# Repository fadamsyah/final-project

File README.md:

# final-project
Control of Autonomous Golf Cart. This repository includes low-level controller and high-level controller.

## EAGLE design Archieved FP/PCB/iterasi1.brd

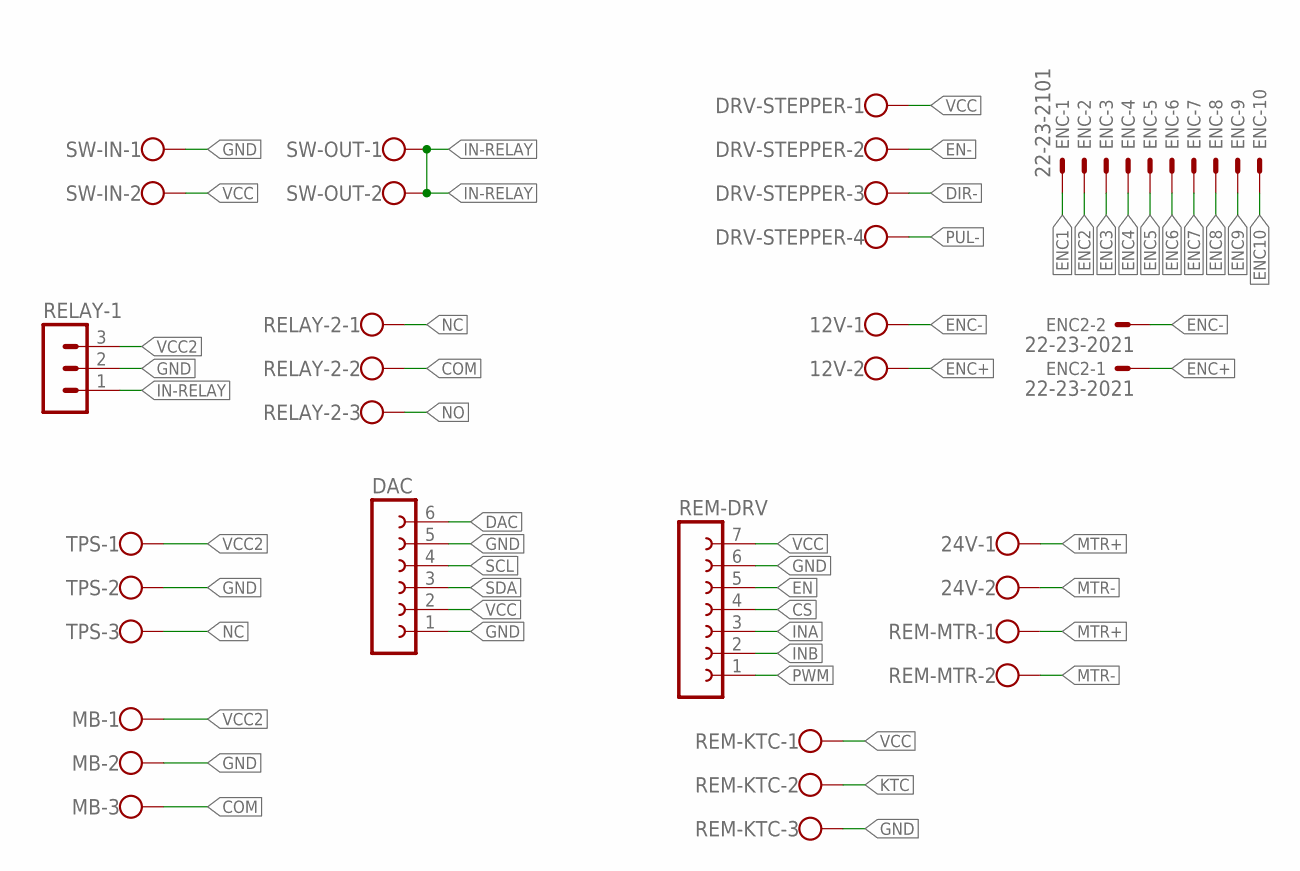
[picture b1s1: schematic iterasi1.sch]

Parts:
12V, 24V: W237-102
DAC: FE06-1; FE06
DRV-STEPPER: W237-4
ENC: 22-23-2101
ENC2: 22-23-2021
MB: W237-103
RELAY-1: MA03-1
RELAY-2: W237-103
REM-DRV: FE07-1; FE07
REM-KTC: W237-103
REM-MTR: W237-102
SW-IN: W237-102
SW-OUT: W237-102
TPS: W237-103

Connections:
COM: MB.3, RELAY-2.2
CS: REM-DRV.4
DAC: DAC.6
DIR-: DRV-STEPPER.3
EN: REM-DRV.5
EN-: DRV-STEPPER.2
ENC1: ENC.1
ENC2: ENC.2
ENC3: ENC.3
ENC4: ENC.4
ENC5: ENC.5
ENC6: ENC.6
ENC7: ENC.7
ENC8: ENC.8
ENC9: ENC.9
ENC10: ENC.10
ENC+: 12V.2, ENC2.1
ENC-: 12V.1, ENC2.2
GND: DAC.1, DAC.5, MB.2, RELAY-1.2, REM-DRV.6, REM-KTC.3, SW-IN.1, TPS.2
IN-RELAY: RELAY-1.1, SW-OUT.1, SW-OUT.2
INA: REM-DRV.3
INB: REM-DRV.2
KTC: REM-KTC.2
MTR+: 24V.1, REM-MTR.1
MTR-: 24V.2, REM-MTR.2
NC: RELAY-2.1, TPS.3
NO: RELAY-2.3
PUL-: DRV-STEPPER.4
PWM: REM-DRV.1
SCL: DAC.4
SDA: DAC.3
VCC: DAC.2, DRV-STEPPER.1, REM-DRV.7, REM-KTC.1, SW-IN.2
VCC2: MB.1, RELAY-1.3, TPS.1

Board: 2 copper layers, 15 parts (0 on the bottom side), 10 nets, no tracks yet.

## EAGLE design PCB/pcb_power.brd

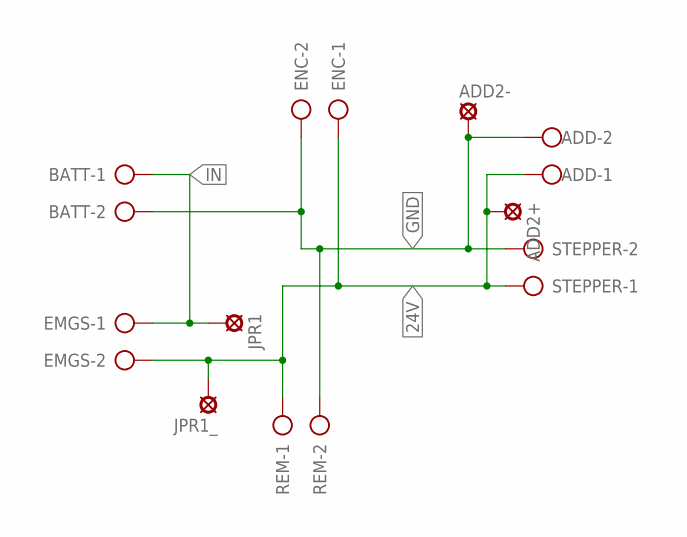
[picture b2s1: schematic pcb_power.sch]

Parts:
ADD: W237-102
ADD2+, ADD2-: SE14
BATT: W237-102
EMGS: W237-102
ENC: W237-102
JPR1, JPR1_: SE14
REM: W237-102
STEPPER: W237-102

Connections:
24V: ADD.1, ADD2+.MP, EMGS.2, ENC.1, JPR1_.MP, REM.1, STEPPER.1
GND: ADD.2, ADD2-.MP, BATT.2, ENC.2, REM.2, STEPPER.2
IN: BATT.1, EMGS.1, JPR1.MP

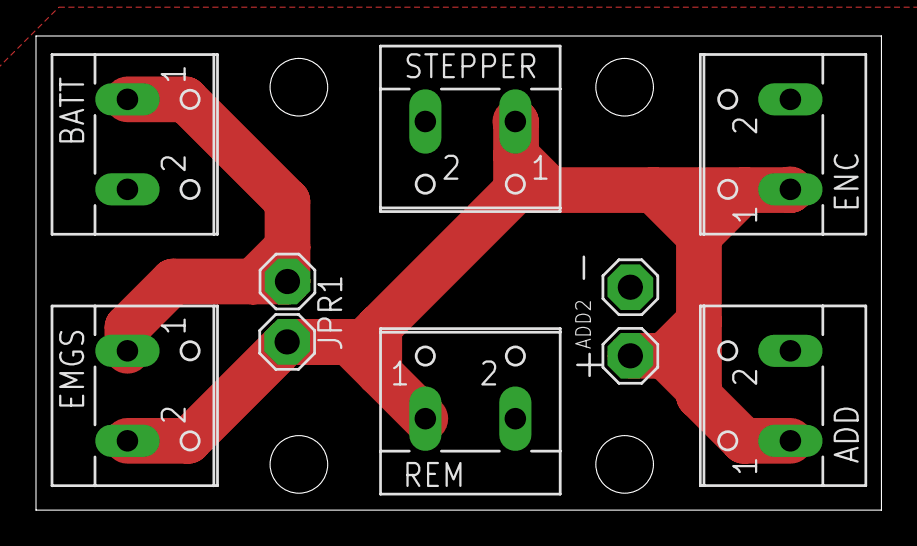
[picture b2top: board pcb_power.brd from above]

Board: 2 copper layers, 47.0 x 26.3 mm, 10 parts (0 on the bottom side), 3 nets.

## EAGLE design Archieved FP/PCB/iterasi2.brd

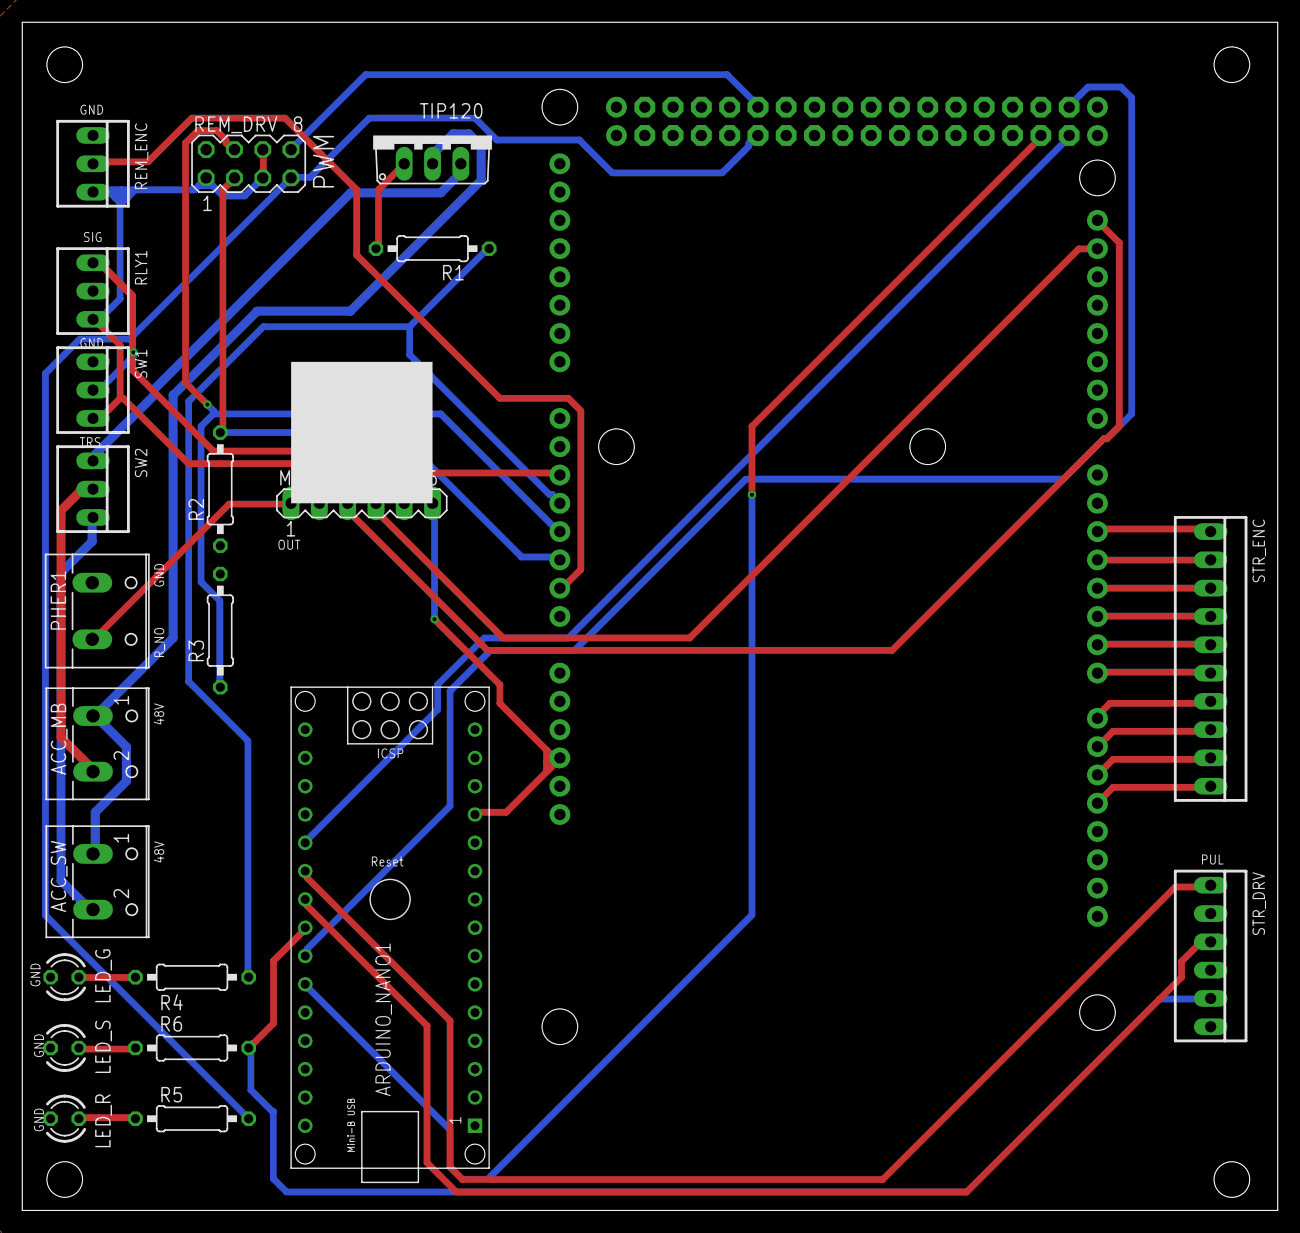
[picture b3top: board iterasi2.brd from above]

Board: 2 copper layers, 112.7 x 106.7 mm, 23 parts (1 on the bottom side), 36 nets.

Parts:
ACC_MB: W237-102
ACC_SW: W237-102
ARDUINO_NANO1: ARDUINO_NANO
B1: ARDUINO_MEGA_R3FULL; ARDUINO_MEGA
LED_G: TLLY4400; LED3MM
LED_R: TLLY4400; LED3MM
LED_S: TLLY4400; LED3MM
MCP4725: MA06-1
PHER1: GND_TPS/RELAY_NO; W237-132
R1: 5k1; 0207/10
R2, R3: 680; 0207/10
R4, R5, R6: 220; 0207/10
REM_DRV: MA04-2
REM_ENC: 22-23-2031
RLY1: 22-23-2031
STR_DRV: 22-23-2061
STR_ENC: 22-23-2101
SW1, SW2: 22-23-2031
TIP120: TIP41C; TO220AV

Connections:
5V: ARDUINO_NANO1.12, B1.5V@0, MCP4725.6, REM_DRV.1, REM_DRV.5, REM_DRV.6, REM_ENC.3, RLY1.3, SW1.3
48V: ACC_MB.1, ACC_SW.1, TIP120.C
F_MODE: B1.A5, RLY1.1, SW1.2
GAS_EN: B1.A4, R1.1, R4.2
GAS_SIG: MCP4725.1, PHER1.2
GND: ARDUINO_NANO1.14, ARDUINO_NANO1.19, B1.GND@0, B1.GND@1, B1.GND@2, B1.GND@3, B1.GND@4, LED_G.K, LED_R.K, LED_S.K, MCP4725.2, MCP4725.5, PHER1.1, R2.1, R3.2, REM_DRV.2, REM_ENC.1, RLY1.2, STR_DRV.2, STR_DRV.4, STR_DRV.6, SW1.1
L_IS: B1.A3, R3.1, REM_DRV.4
L_PWM: B1.45, REM_DRV.8
unnamed: R1.2, TIP120.B
unnamed: SW2.1, TIP120.E
unnamed: ACC_MB.2, SW2.2
unnamed: ACC_SW.2, SW2.3
unnamed: LED_G.A, R4.1
unnamed: LED_R.A, R5.1
unnamed: LED_S.A, R6.1
unnamed: ARDUINO_NANO1.20, B1.22
unnamed: ARDUINO_NANO1.24, B1.23
unnamed: ARDUINO_NANO1.25, B1.24
REM_ENC: B1.A1, REM_ENC.2
R_IS: B1.A2, R2.2, REM_DRV.3
R_PWM: B1.44, R5.2, REM_DRV.7
SCL: B1.21, MCP4725.3
SDA: B1.20, MCP4725.4
SEN1: B1.2, STR_ENC.1
SEN2: B1.3, STR_ENC.2
SEN3: B1.4, STR_ENC.3
SEN4: B1.5, STR_ENC.4
SEN5: B1.6, STR_ENC.5
SEN6: B1.7, STR_ENC.6
SEN7: B1.8, STR_ENC.7
SEN8: B1.9, STR_ENC.8
SEN9: B1.10, STR_ENC.9
SEN10: B1.11, STR_ENC.10
STR_DIR: ARDUINO_NANO1.22, STR_DRV.3
STR_ENA: ARDUINO_NANO1.23, R6.2, STR_DRV.5
STR_PUL: ARDUINO_NANO1.21, STR_DRV.1

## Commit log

2020-07-24 - Make the low-level-controller - Add the brake_log_mega using BTS 7960 driver
2020-07-24 Add a ROS package named 'pkg_ta'
2020-07-24 Add two additional informations to the message: 1) string brake_state 2) string steering_state
    Change some data type of the informations of brake:
    1) brake_linear_encoder ~ int32 --> float32
    2) signal from current sensor ~ int32 --> float32
    Add right and left current sensor:
    1) float32 brake_R_IS
    2) float32 brake_L_IS
2020-07-24 Update the brake_log_mega_bts7960 including: 1) Add some additional informations to the Brake message 2) Divide the sensing_braking into sensing_braking_position & sensing_braking_current
2020-07-24 Add mega_implementation.ino
2020-07-24 Add the mega_implementation.ino
2020-07-25 Add the stepper_nano.ino file
2020-07-25 Optimize the stepper_nano file and fix a prospective bug 1) Delete all of the unnecessary line, e.g. Serial.begin and Serial.println 2) Change a variable name, i.e. now --> dt 3) Fix a prospective bu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
2020-07-29 Add the ROX.txt file and update the mega_implementation: 1) Add the throttle code in mega_implementation 2) Comment the state message in Arduino because of error. The string message should be sent co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
2020-08-02 Add the pre-made drawio file describing the diagram block
2020-08-03 Initialize the data branch
2020-08-03 Add some files: 1. .gitignore files ignoring .ipynb_checkpoints 2. Add the absolute encoder calibration data and notebook 3. Add the linear transduser calibration data 4. Add the rosbag data
2020-08-03 Make some linear regression models for absolute encoder and linear transduser sensor
2020-08-05 Add the absolute encoder calibration
2020-08-05 Add a .ipynb estimating how long the Arduino takes to accelerate the stepper motor and optimize the stepper motor code.
2020-08-06 Edit the calibration plot
2020-08-06 Convert the steering angle from radian to degree
2020-08-07 Change the maximum and minimum value command from a joystitck
2020-08-07 Add the .gitignore file ignoring .ipynb_checkpoints/ and __pycache__/
2020-08-07 Add the controller_2D.py file as the high level controller
2020-08-07 Add the UNCOMPLETE control.py file
2020-08-09 Add the waypoints
2020-08-09 Use the exponential moving average algorithm to make the joystick signal smoother.
2020-08-09 Edit the .gitignore file
2020-08-10 Test the joystick.py, fix some bugs in that file, and add the steer, throttle, and brake threshold.
2020-08-10 Add some additional variables into Control.msg and edit the joystick.py
2020-08-10 Change the sub_msg.<var> to sub_msg.action_<var> in Arduino to match the newest Control.msg
2020-08-11 Fix some bugs, i.e.: 1) Change the DIR dan PUL pin 2) Change the stepper acceleration 3) Make the Arduino Mega sends the interrupt signal to the Arduino Mega every update_steering_period
2020-08-11 Make two different coefficients to calculate the longitudinal dan lateral control signal using exponential moving average (EMA)
2020-08-11 Add the control deadband to control the steering angle
2020-08-11 Laporan TA @11 August 2020
2020-08-12 Evaluation @ 12 August 2020: 1. Change steering_delta_min_move to 0.3 degree 2. Change the acceleration of the stepper motor 3. Change the max_throttle to 0.5 in joystick.py file 4. Add the log_steer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
2020-08-12 Analyze and visualize the movement of steering angle.
2020-08-13 Add some additional lines to the UNOMPLETED control.py file
2020-08-13 Edit the PWM setting in the log_brake.ino file
2020-08-13 Add the UNCOMPLETE brake calibration
2020-08-13 Evaluation @13 August 2020: 1) Add the LogBrakeCommand.msg 2) Edit the CMakeLists.txt to include LogBrakeCommand.msg 3) Edit the maximum throttle value in joystick.py 4) Add the log_brake.py and the 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
2020-08-13 Compare the Quaternion --> RPY Conversion from tf and Coursera
2020-08-13 Add the interpolated waypoints
2020-08-13 Complete the control.py file, add the waypoints, and move the log python file to the /log_low_level/ folder
2020-08-14 Limit the change of the throttle voltage
2020-08-14 Change the maximum value of the throttle output
2020-08-14 Plot the brake data
2020-08-14 Add the pwm sign to brake_pwm so that we know whether the motor is PULLING or RELEASING
2020-08-14 Edit the architecture of steering control
2020-08-15 Add some additional information regarding the steering and brake performance
2020-08-17 Add the kalman filter for estimate the state from GPS data only
2020-08-17 Add the kf_gps class optimized using Numba
2020-08-17 ROS Error. Save file dulu
2020-08-17 Add the ROS gps state estimation program
2020-08-17 Add the angular rate correction
2020-08-17 Add the waypoints' bag
2020-08-17 Add the kf_gps test
2020-08-18 Generate some new waypoints
2020-08-18 Add the new lab waypoints
2020-08-18 pkg_ta MAJOR CHANGE: 1) Move the controller_2D.py and kf_gps.py (containing some classes) to lib_ta_py/ 2) Solve a bug regarding the lateral saturation value in controller_2D.py 3) Make the bag/ fold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
2020-08-19 MAJOR UPDATE: 1) Add new generate_waypoints_CEPAT folder 2) Log step response 3) Tune the stanley controller in control_with_gps.py 4) Ada data yang berhasil diambil (lateral control)
2020-08-19 Add step response data & 2 percobaan yang berhasil (lateral control)
2020-08-19 Plot beberapa informasi menarik
2020-08-19 Cek data longitudinal yang dikirim Atwin
2020-08-20 Add some plots regarding the result of 'data_yang_berhasil'
2020-08-22 Add some plot to log_longitudinal/dari_atwin/cek_data.ipynb
2020-08-22 Add a CARLA simulation folder
2020-08-22 Add the simulation plot and result
2020-08-22 Fix some bugs
2020-08-22 Organize some files and add the longitudinal data
2020-08-23 Get longitudinal data for simulation
2020-08-24 Add some new log steering data
2020-08-24 Edit the stepper timing and add some code to overcome the stepper stalling phenomena
2020-08-24 pkg_TA @24 August 2020
2020-08-25 Progress @25 August 2020
2020-08-25 PROGRESS @25 Agustus 2020
2020-08-25 Add some additional analysis
2020-08-26 PROGRESS @26 Agustus 2020
2020-08-26 Add some additional experiment data (26 Agustus 2020)
2020-08-26 Lateral Control with error lateral only: Proportional-Derivative
2020-08-26 Add additional data and code to generate waypoints
2020-08-26 New ROS-control file for final project
2020-08-26 Add a .ipynb that generate a new set of waypoints from the 26_agus_wp by shifting the initial position
2020-08-26 Fix a bug. The x and y shift must be calculated at a specific point for every set of waypoints
2020-08-27 Progress 27 Agustus 2020 (PAGI)
2020-08-27 Plot some experiment results
2020-08-27 PROGRESS @ 27 Agustus 2020
2020-08-28 Make the EDIT_WAYPOINTS notebook to automatically update all of the set of waypoints. Add some new codes
2020-08-28 Edit some codes
2020-08-28 Add the newest LAPORAN TUGAS AKHIR file
2020-08-29 PROGRESS @28 Agustus 2020
2020-08-29 Make some visualizations of waypoints
2020-08-29 Add DAC calibration data
2020-08-29 Edit image
2020-08-29 Try EKF with IMU and GNSS
2020-08-30 Analyze the experiment data. The GNSS bias can make the estimated yaw angle drift !
2020-08-30 Optimize the ekf_imu_2d code
2020-08-30 Add GPS Averager
2020-08-30 Add PCB
2020-08-30 MAJOR UPDATE
2020-08-31 Add a additional data to State_EKF_2D.msg
2020-08-31 Edit some python files
2020-08-31 Edit ekf_imu_2d.py
2020-08-31 Add some new waypoints
2020-08-31 Add log data @31 Agustus 2020
2020-08-31 Add the longitudinal control plot
2020-08-31 Plot the newest waypoints
2020-09-01 Edit the timing of stepper motor
2020-09-01 New Waypoints
2020-09-02 Edit the waypoints, use throttle instead of velocity & add the lateral control data
2020-09-02 update the steering dynamics data
2020-09-03 Add some lateral data plots
2020-09-03 MAJOR UPDATE: Experiment Results
2020-09-03 Cek the initial error
2020-09-03 Add some simulation data
2020-09-03 Add a simulation code using PID as the lateral controller
2020-09-04 Edit steering block diagram
2020-09-04 Edit some diagrams
2020-09-05 Edit a diagram
2020-09-05 Add the generating waypoints plot
2020-09-10 Data 10 September 2020
2020-09-11 Add some new data
2020-09-11 Add some new plots
2020-09-12 Edit
2020-09-17 Add the monev folder
2020-09-25 Renew the pkg_ta folder

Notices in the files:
parts and their libraries:
SparkFun-Boards: Licensing: Creative Commons ShareAlike 4.0 International - https://creativecommons.org/licenses/by-sa/4.0
